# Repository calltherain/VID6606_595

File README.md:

VID6606_595 KiCad projects
===========

the VID6606_595 schema and PCB

Download and compile KiCad by using KiCad_Winbuilder below to open files because the component footprint used in this project has been migrated to the new .pretty format.
https://launchpad.net/kicad-winbuilder

Now KiCad default build has no footprint libraries attached but the libraries were released on github, 
https://www.github.com/KiCad
you MUST do this step so KiCad can read the libraries from github directly:
copy this file

   d:\kicad-winbuilder-3.4\kicad\share\template\fp-lib-table.for-github
   
to this place, ( remove ".for-github" from the file name )

   %userprofile%\appdata\roaming\kicad\fp-lib-table
   
This will tell KiCad-CvPCB to read the footprint (modules) from github.

If you don't want to mess with the schema or the PCB design you can just go to gerber folder and send the files to PCB manufactures to build the sample board.

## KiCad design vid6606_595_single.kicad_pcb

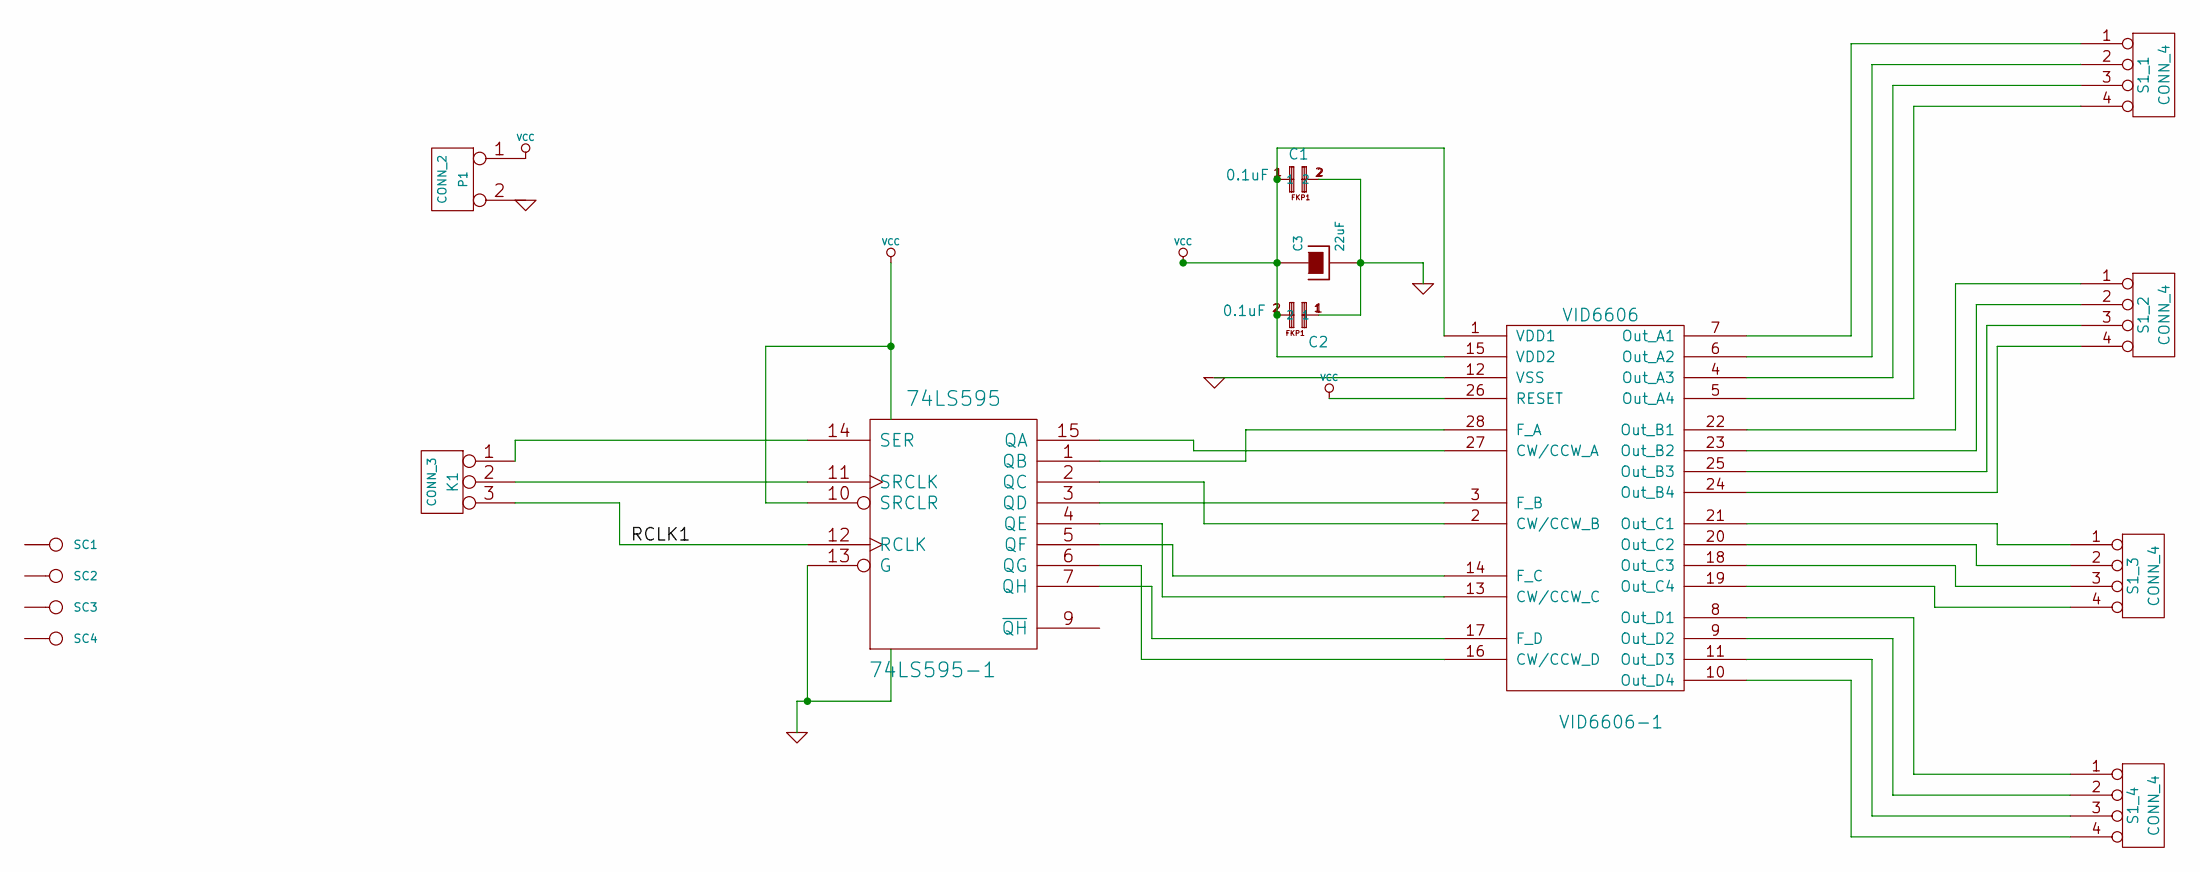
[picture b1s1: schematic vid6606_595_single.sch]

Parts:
74LS595-1: 74LS595
C1, C2: 0.1uF; Capacitor-Wima-FKP1-400v-R22K5B10
C3: 22uF
K1: CONN_3
P1: CONN_2
S1_1, S1_2, S1_3, S1_4: CONN_4
SC1, SC2, SC3, SC4: CONN_1
VID6606-1: VID6606

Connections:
/RCLK1: 74LS595-1.12 (RCLK), K1.3
GND: 74LS595-1.8 (GND), 74LS595-1.13 (G), C1.2, C2.1, C3.2, P1.2 (PM), VID6606-1.12 (VSS)
unnamed: 74LS595-1.14 (SER), K1.1
unnamed: 74LS595-1.7 (QH), VID6606-1.17 (F_D)
unnamed: 74LS595-1.11 (SRCLK), K1.2 (PM)
unnamed: 74LS595-1.5 (QF), VID6606-1.14 (F_C)
unnamed: 74LS595-1.6 (QG), VID6606-1.16 (CW/CCW_D)
unnamed: S1_4.4, VID6606-1.10 (Out_D4)
unnamed: S1_3.2, VID6606-1.20 (Out_C2)
unnamed: S1_4.3, VID6606-1.11 (Out_D3)
unnamed: S1_3.1, VID6606-1.21 (Out_C1)
unnamed: S1_2.1, VID6606-1.22 (Out_B1)
unnamed: 74LS595-1.4 (QE), VID6606-1.13 (CW/CCW_C)
unnamed: S1_2.2, VID6606-1.23 (Out_B2)
unnamed: S1_2.4, VID6606-1.24 (Out_B4)
unnamed: S1_2.3, VID6606-1.25 (Out_B3)
unnamed: S1_4.2, VID6606-1.9 (Out_D2)
unnamed: 74LS595-1.15 (QA), VID6606-1.27 (CW/CCW_A)
unnamed: S1_3.3, VID6606-1.18 (Out_C3)
unnamed: 74LS595-1.1 (QB), VID6606-1.28 (F_A)
unnamed: S1_3.4, VID6606-1.19 (Out_C4)
unnamed: S1_1.1, VID6606-1.7 (Out_A1)
unnamed: S1_1.2, VID6606-1.6 (Out_A2)
unnamed: 74LS595-1.2 (QC), VID6606-1.2 (CW/CCW_B)
unnamed: 74LS595-1.3 (QD), VID6606-1.3 (F_B)
unnamed: S1_1.3, VID6606-1.4 (Out_A3)
unnamed: S1_1.4, VID6606-1.5 (Out_A4)
unnamed: S1_4.1, VID6606-1.8 (Out_D1)
VCC: 74LS595-1.10 (SRCLR), 74LS595-1.16 (VCC), C1.1, C2.2, C3.1, P1.1, VID6606-1.1 (VDD1), VID6606-1.15 (VDD2), VID6606-1.26 (RESET)

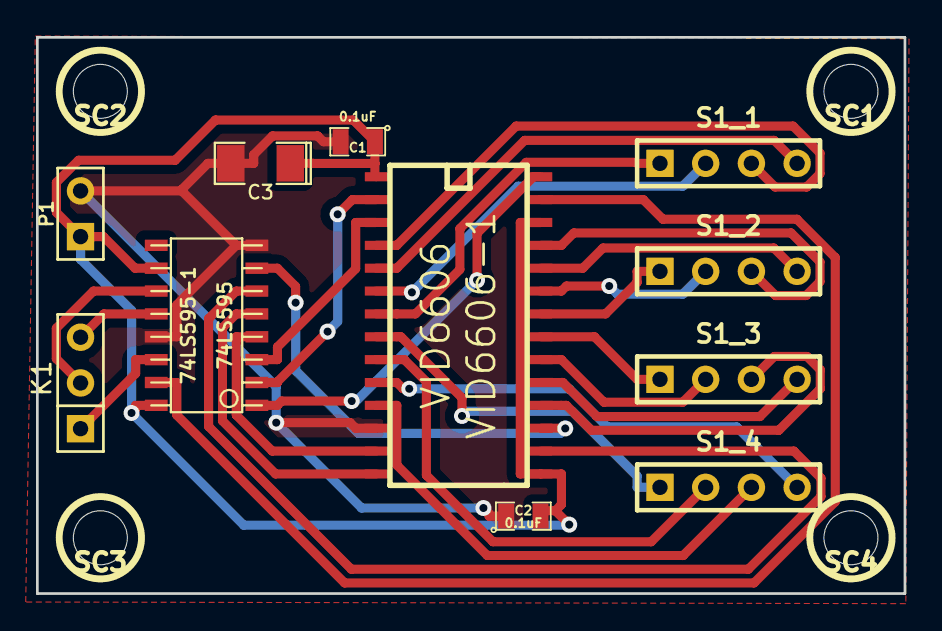
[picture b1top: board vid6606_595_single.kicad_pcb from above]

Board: 2 copper layers, 48.2 x 30.9 mm, 15 parts (0 on the bottom side), 29 nets.

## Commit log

2014-09-24 :space_invader: Added .gitattributes & .gitignore files
2014-09-24 add files to git
2014-09-24 Create LICENSE
2014-10-03 fix the CvPCB associates, added Gerber Files in case you want to build the board without changing it
